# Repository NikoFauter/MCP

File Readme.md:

Team: t02
Name: Niko Fauter
Course of Studies: Electrical Engineering
Semester: SS23

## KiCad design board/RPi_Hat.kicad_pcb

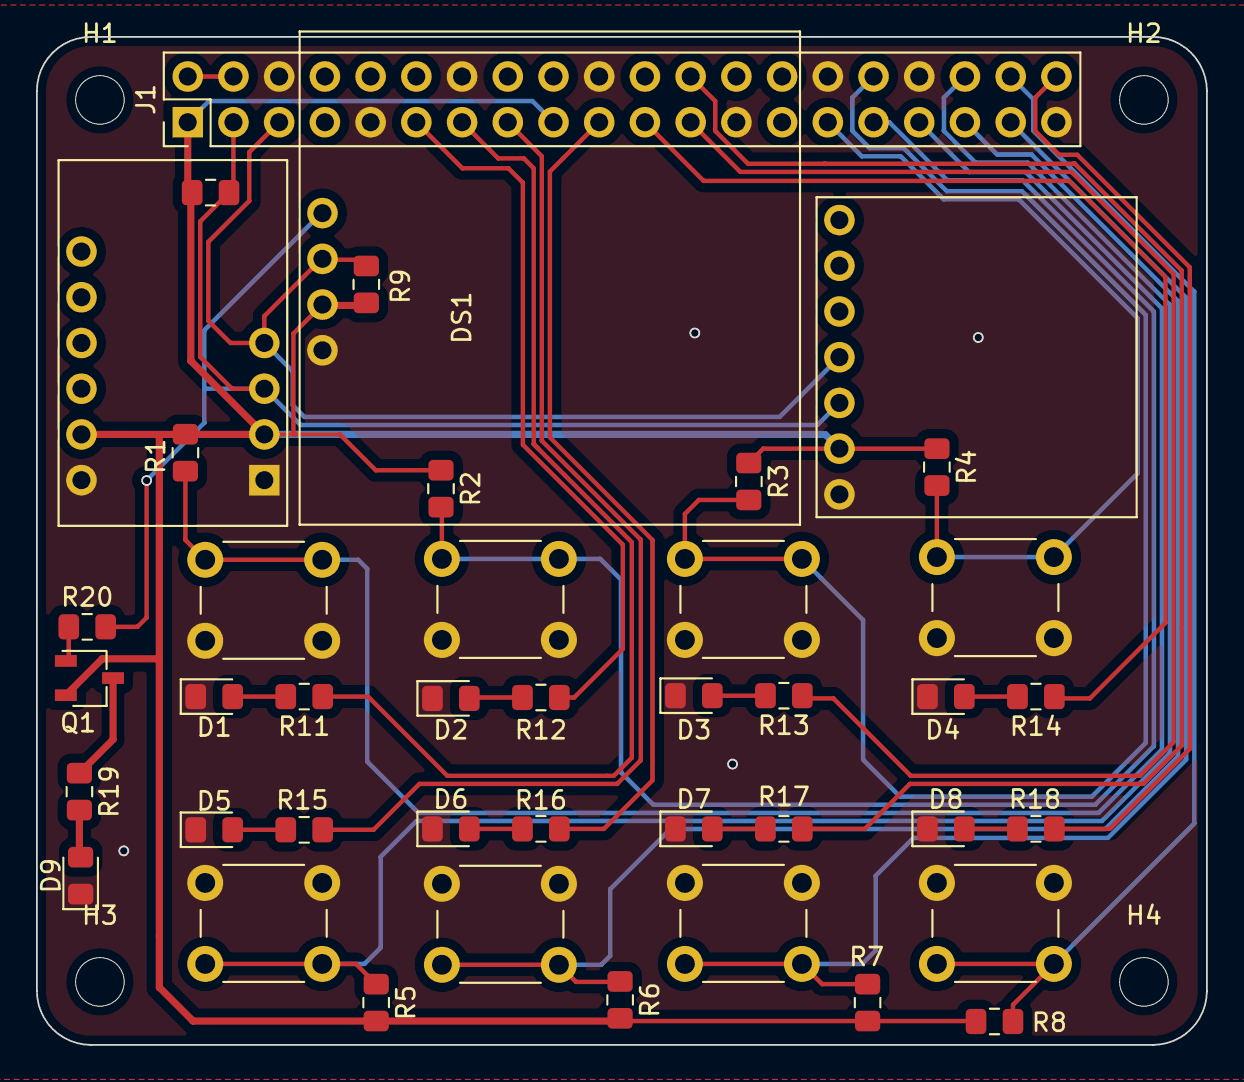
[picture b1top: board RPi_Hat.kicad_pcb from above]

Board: 2 copper layers, 65.0 x 56.0 mm, 46 parts (0 on the bottom side), 32 nets.

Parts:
A1: Sparkfun-CCS811; Sparkfun-CCS881
A2: BME280
D1, D2, D3, D4, D5, D6, D7, D8: red; LED_0805
D9: green; LED_0805
DS1: OLED
H1, H2, H3, H4: MountingHole; MountingHole_2.7mm_M2.5
J1: PiHat; PiHeader
Q1: PMOS_GSD; SOT-23
R1, R2, R3, R4, R5, R6, R7, R8, R9, R10: 10k; R_0805
R11, R12, R13, R14, R15, R16, R17, R18: 330; R_0805
R19: 200; R_0805
R20: 100; R_0805
SW1, SW2, SW3, SW4, SW5, SW6, SW7, SW8: Pushbutton; PushButton

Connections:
+3V3: A1.2 (3V3), A2.2 (VCC), A2.6 (VCC), DS1.2 (VCC), J1.1 (3.3V), J1.17 (3.3V), Q1.2 (S), R1.1, R2.1, R3.1, R4.1, R5.1, R6.1, R7.1, R8.1, R9.1, R10.1
+5V: J1.2 (5V), J1.4 (5V)
Button 1: J1.33 (PB1), R1.2, SW1.2
Button 2: J1.31 (PB2), R2.2, SW2.2
Button 3: J1.32 (PB3), R3.2, SW3.2
Button 4: J1.29 (PB4), R4.2, SW4.2
Button 5: J1.36 (PB5), R5.2, SW5.2
Button 6: J1.35 (PB6), R6.2, SW6.2
Button 7: J1.37 (PB7), R7.2, SW7.2
Button 8: J1.38 (PB8), R8.2, SW8.2
Diode 1: J1.13 (D1), R11.1
Diode 2: J1.11 (D2), R12.1
Diode 3: J1.23 (D3), R13.1
Diode 4: J1.21 (D4), R14.1
Diode 5: J1.15 (D5), R15.1
Diode 6: J1.19 (D6), R16.1
Diode 7: J1.24 (D7), R17.1
Diode 8: J1.40 (D8), R18.1
GND: A1.1 (GND), A2.1 (GND), A2.5 (GND), D1.1 (K), D2.1 (K), D3.1 (K), D4.1 (K), D5.1 (K), D6.1 (K), D7.1 (K), D8.1 (K), D9.1 (K), DS1.1 (GND), J1.6 (GND), J1.9 (GND), J1.14 (GND), J1.20 (GND), J1.25 (GND), J1.30 (GND), J1.34 (GND), J1.39 (GND), SW1.1, SW2.1, SW3.1, SW4.1, SW5.1, SW6.1, SW7.1, SW8.1
unnamed: D1.2 (A), R11.2
unnamed: D2.2 (A), R12.2
unnamed: D3.2 (A), R13.2
unnamed: D4.2 (A), R14.2
unnamed: D5.2 (A), R15.2
unnamed: D6.2 (A), R16.2
unnamed: D7.2 (A), R17.2
unnamed: D8.2 (A), R18.2
unnamed: D9.2 (A), R19.2
unnamed: Q1.1 (G), R20.1
unnamed: Q1.3 (D), R19.1
SCL: A1.4 (SCL), A2.4 (SCL), DS1.3 (SCL), J1.5 (SCL), R9.2
SDA: A1.3 (SDA), A2.3 (SDA), DS1.4 (SDA), J1.3 (SDA), R10.2, R20.2

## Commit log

2022-05-08 First commit as test
2022-05-12 finished schematic
2022-05-17 pcb_completly_wired
2022-05-23 transistors
2022-05-23 finalisation
2022-05-23 reinserted correct scematic
2022-05-23 some bugfixing
2022-05-26 last minor changes
2022-05-29 added Diode to monitor SDA
2022-05-29 Made some wires Bigger
2022-05-31 first steps with the code
2022-06-02 progress in bme280.py
2022-06-03 final version
2022-06-03 finished bme280
2022-06-04 some formating changes
2022-06-04 something in css I guess
2022-06-11 code
2022-06-11 nothing
2022-06-13 added to app.py
2022-06-13 further additions to app.py
2022-07-12 making it work again
